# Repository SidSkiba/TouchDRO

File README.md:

# TouchDRO
TocuhDRO PCB Kicad Design

PCB Design Files for a DIY TouchDRO PCB. This is based on information provided by https://www.touchdro.com/

All design done in Kicad 8.

Firmware files provided by https://www.touchdro.com/

All Gerber files included for JLCPCB to manufacture the circuit boards.

Design uses some surface mount components (some 0805 sized resistors and capacitors and sirface mount IC's) so you need to be comfortable with soldering those devices to the board.

Note that ESP32 module needs to be spaced 5mm above the circuit board.

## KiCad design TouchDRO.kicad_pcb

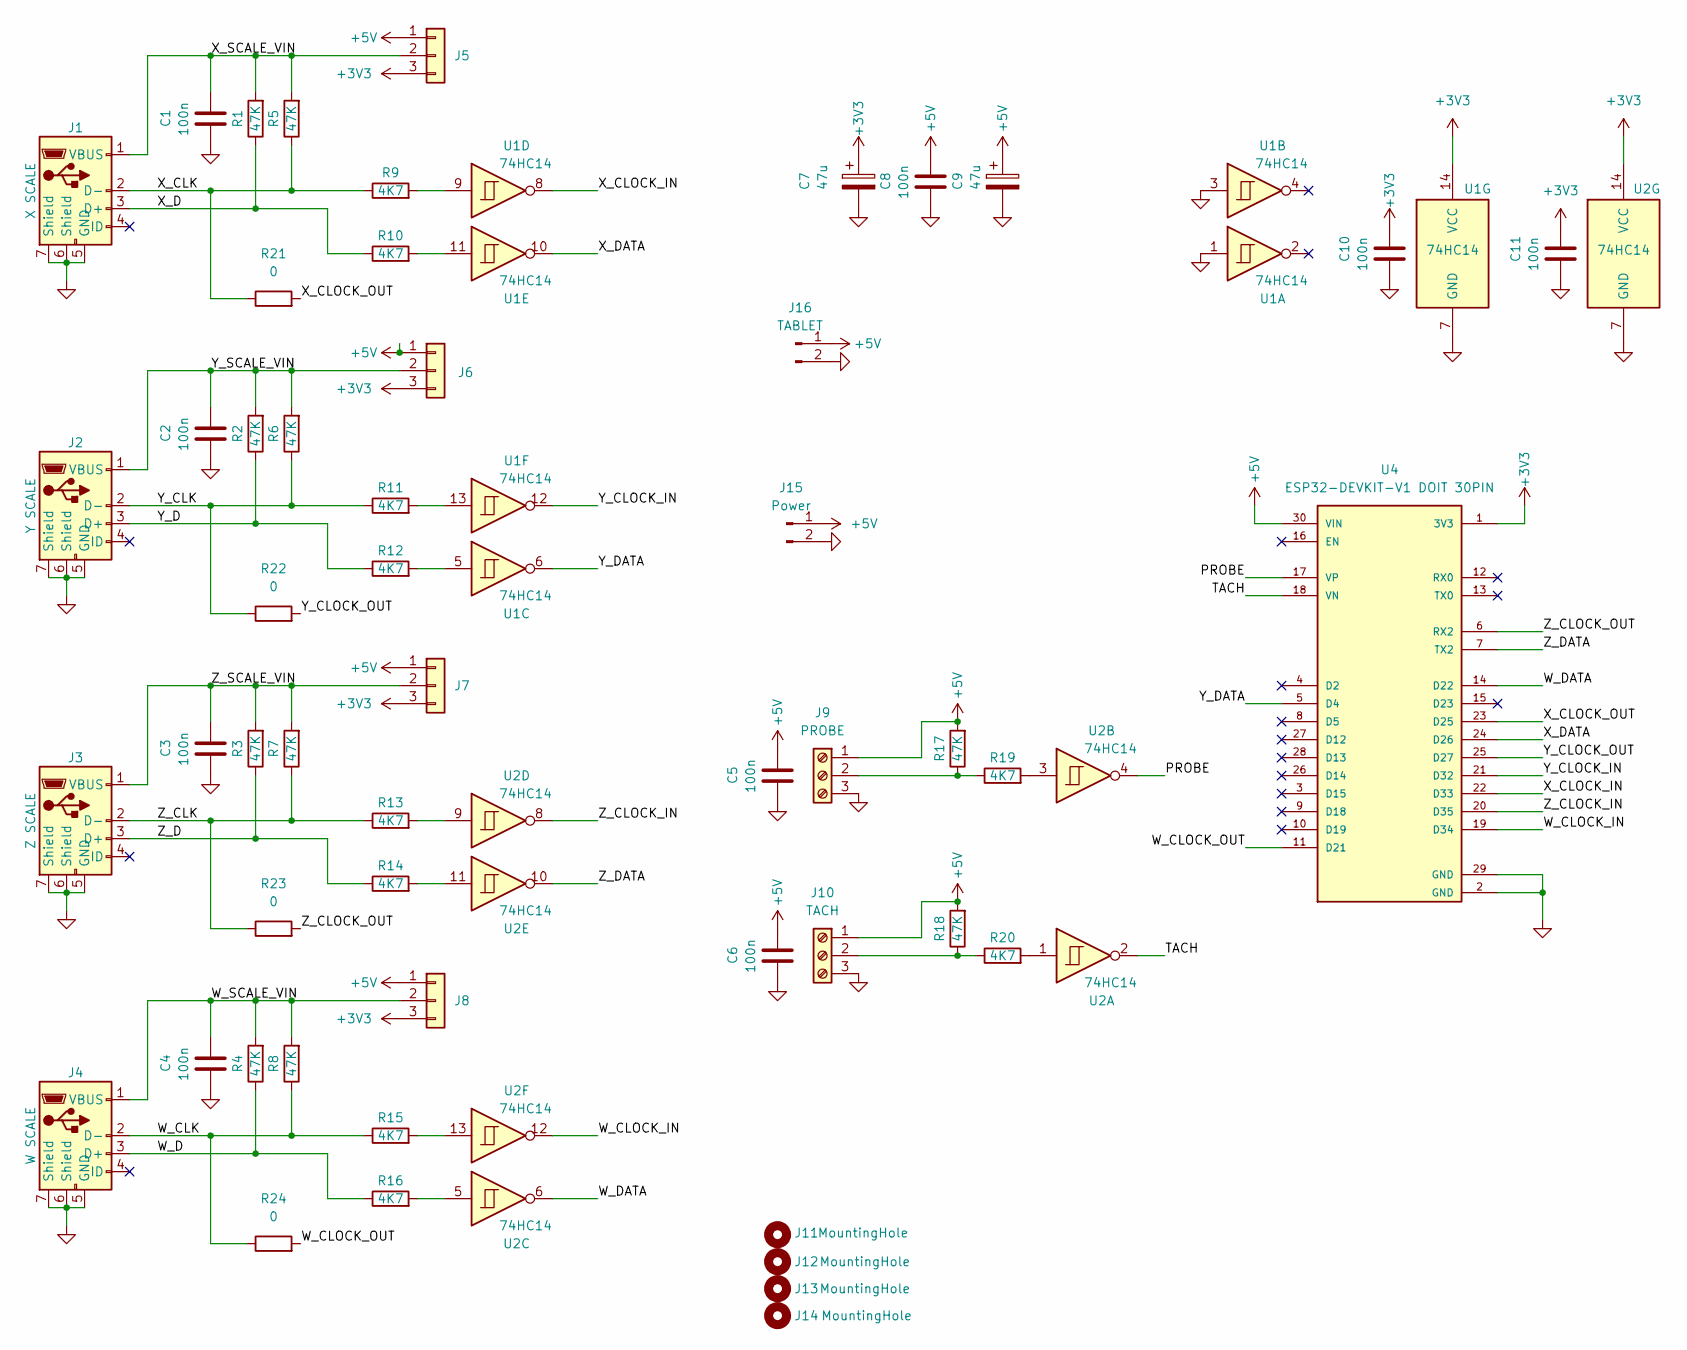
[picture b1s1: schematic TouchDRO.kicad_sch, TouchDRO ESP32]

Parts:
C1, C2, C3, C4, C5, C6, C8, C10, C11: 100n; C_0805_2012Metric_Pad1.18x1.45mm_HandSolder; LCSC C3034534
C7, C9: 47u; CP_Radial_D8.0mm_P3.50mm; LCSC 03EC0571
J1: X SCALE; USB Breakout Board
J2: Y SCALE; USB Breakout Board
J3: Z SCALE; USB Breakout Board
J4: W SCALE; USB Breakout Board
J5: X SCALE; PinHeader_1x03_P2.54mm_Vertical
J6: Y SCALE; PinHeader_1x03_P2.54mm_Vertical
J7: Z SCALE; PinHeader_1x03_P2.54mm_Vertical
J8: W SCALE; PinHeader_1x03_P2.54mm_Vertical
J9: PROBE; TerminalBlock_Phoenix_MPT-0,5-3-2.54_1x03_P2.54mm_Horizontal
J10: TACH; TerminalBlock_Phoenix_MPT-0,5-3-2.54_1x03_P2.54mm_Horizontal
J11, J12, J13, J14: MountingHole; MountingHole_3.5mm
J15: Power; PinHeader_1x02_P2.54mm_Vertical
J16: TABLET; PinHeader_1x02_P2.54mm_Vertical
R1, R2, R3, R4, R5, R6, R7, R8, R17, R18: 47K; R_0805_2012Metric_Pad1.20x1.40mm_HandSolder; LCSC C410613
R9, R10, R11, R12, R13, R14, R15, R16, R19, R20: 4K7; R_Axial_DIN0204_L3.6mm_D1.6mm_P7.62mm_Horizontal; LCSC C119339
R21, R22, R23, R24: 0; R_Axial_DIN0204_L3.6mm_D1.6mm_P7.62mm_Horizontal
U1, U2: 74HC14; 14PIN_SOIC; LCSC C2907
U4: ESP32-DEVKIT-V1 DOIT 30PIN; MODULE_ESP32_DEVKIT_V1 DOIT 30PIN; PARTREV N/A

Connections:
+3V3: C7.1, C10.1, C11.1, J5.3, J6.3, J7.3, J8.3, U1.14 (VCC), U2.14 (VCC), U4.1 (3V3)
+5V: C5.1, C6.1, C8.1, C9.1, J5.1, J6.1, J7.1, J8.1, J9.1, J10.1, J15.1, J16.1, R17.2, R18.2, U4.30 (VIN)
/PROBE: U2.4, U4.17 (VP)
/TACH: U2.2, U4.18 (VN)
/W_CLK: J4.2 (D-), R8.1, R15.1, R24.1
/W_CLOCK_IN: U2.12, U4.19 (D34)
/W_CLOCK_OUT: R24.2, U4.11 (D21)
/W_D: J4.3 (D+), R4.1, R16.1
/W_DATA: U2.6, U4.14 (D22)
/W_SCALE_VIN: C4.1, J4.1 (VBUS), J8.2, R4.2, R8.2
/X_CLK: J1.2 (D-), R5.1, R9.1, R21.1
/X_CLOCK_IN: U1.8, U4.22 (D33)
/X_CLOCK_OUT: R21.2, U4.23 (D25)
/X_D: J1.3 (D+), R1.1, R10.1
/X_DATA: U1.10, U4.24 (D26)
/X_SCALE_VIN: C1.1, J1.1 (VBUS), J5.2, R1.2, R5.2
/Y_CLK: J2.2 (D-), R6.1, R11.1, R22.1
/Y_CLOCK_IN: U1.12, U4.21 (D32)
/Y_CLOCK_OUT: R22.2, U4.25 (D27)
/Y_D: J2.3 (D+), R2.1, R12.1
/Y_DATA: U1.6, U4.5 (D4)
/Y_SCALE_VIN: C2.1, J2.1 (VBUS), J6.2, R2.2, R6.2
/Z_CLK: J3.2 (D-), R7.1, R13.1, R23.1
/Z_CLOCK_IN: U2.8, U4.20 (D35)
/Z_CLOCK_OUT: R23.2, U4.6 (RX2)
/Z_D: J3.3 (D+), R3.1, R14.1
/Z_DATA: U2.10, U4.7 (TX2)
/Z_SCALE_VIN: C3.1, J3.1 (VBUS), J7.2, R3.2, R7.2
GND: C1.2, C2.2, C3.2, C4.2, C5.2, C6.2, C7.2, C8.2, C9.2, C10.2, C11.2, J1.5 (GND), J1.6 (Shield), J1.7 (Shield), J2.5 (GND), J2.6 (Shield), J2.7 (Shield), J3.5 (GND), J3.6 (Shield), J3.7 (Shield), J4.5 (GND), J4.6 (Shield), J4.7 (Shield), J9.3, J10.3, J15.2, J16.2, U1.1, U1.3, U1.7 (GND), U2.7 (GND), U4.2 (GND), U4.29 (GND)
unnamed: J9.2, R17.1, R19.1
unnamed: J10.2, R18.1, R20.1
unnamed: R9.2, U1.9
unnamed: R10.2, U1.11
unnamed: R11.2, U1.13
unnamed: R12.2, U1.5
unnamed: R13.2, U2.9
unnamed: R14.2, U2.11
unnamed: R15.2, U2.13
unnamed: R16.2, U2.5
unnamed: R19.2, U2.3
unnamed: R20.2, U2.1

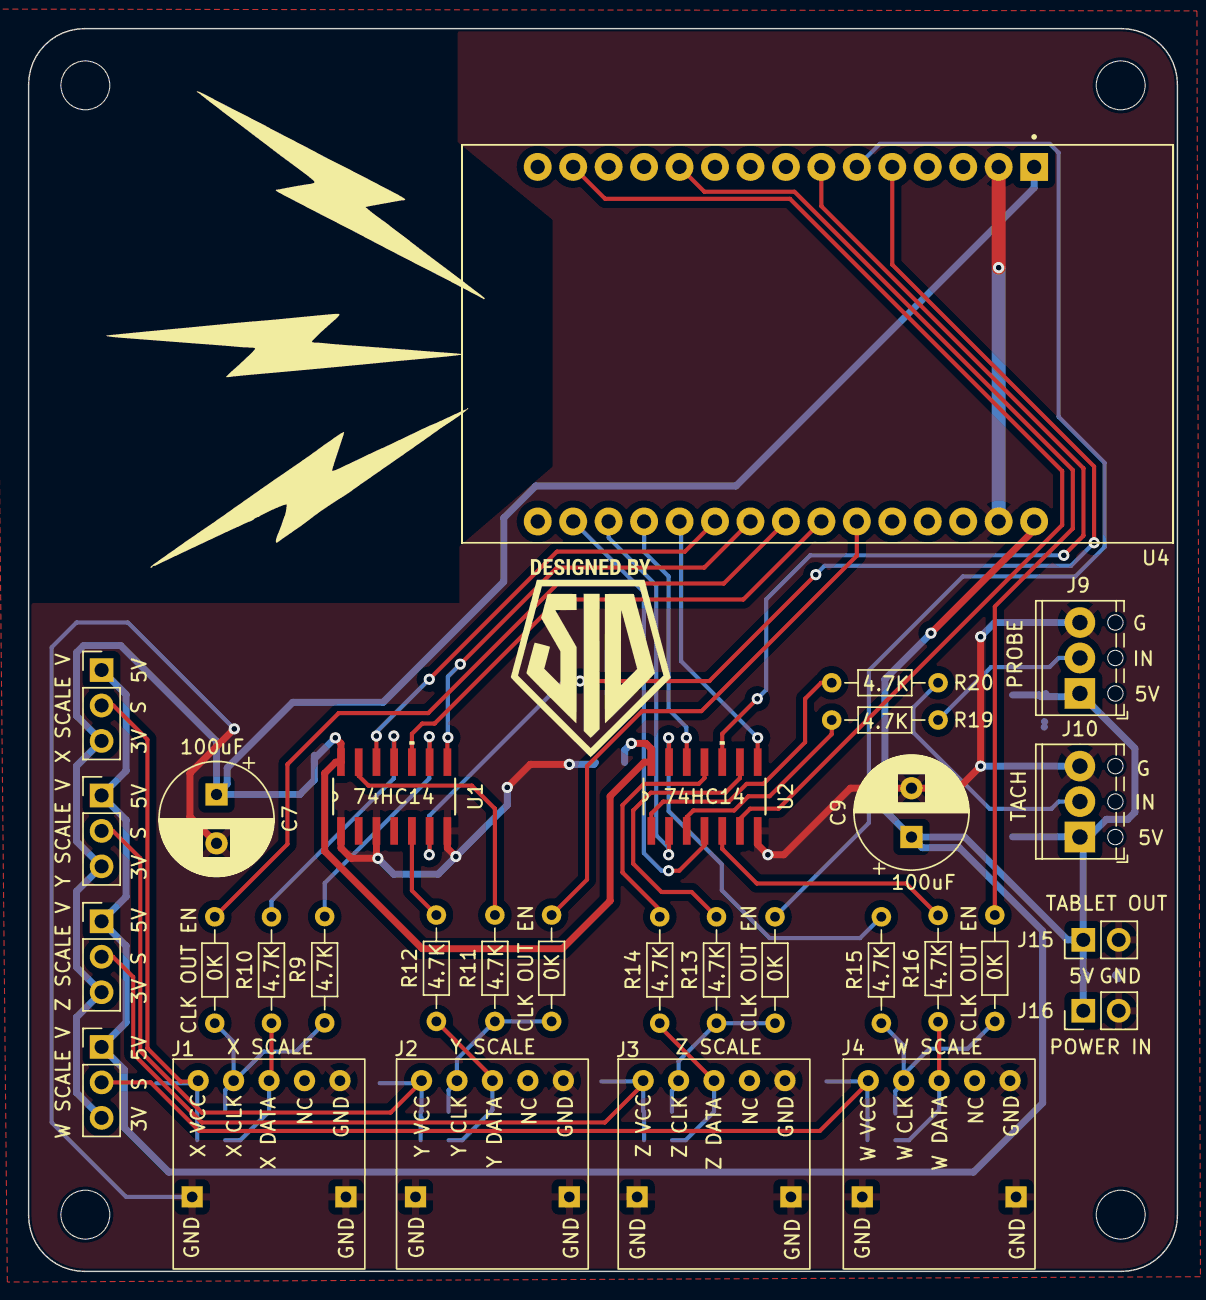
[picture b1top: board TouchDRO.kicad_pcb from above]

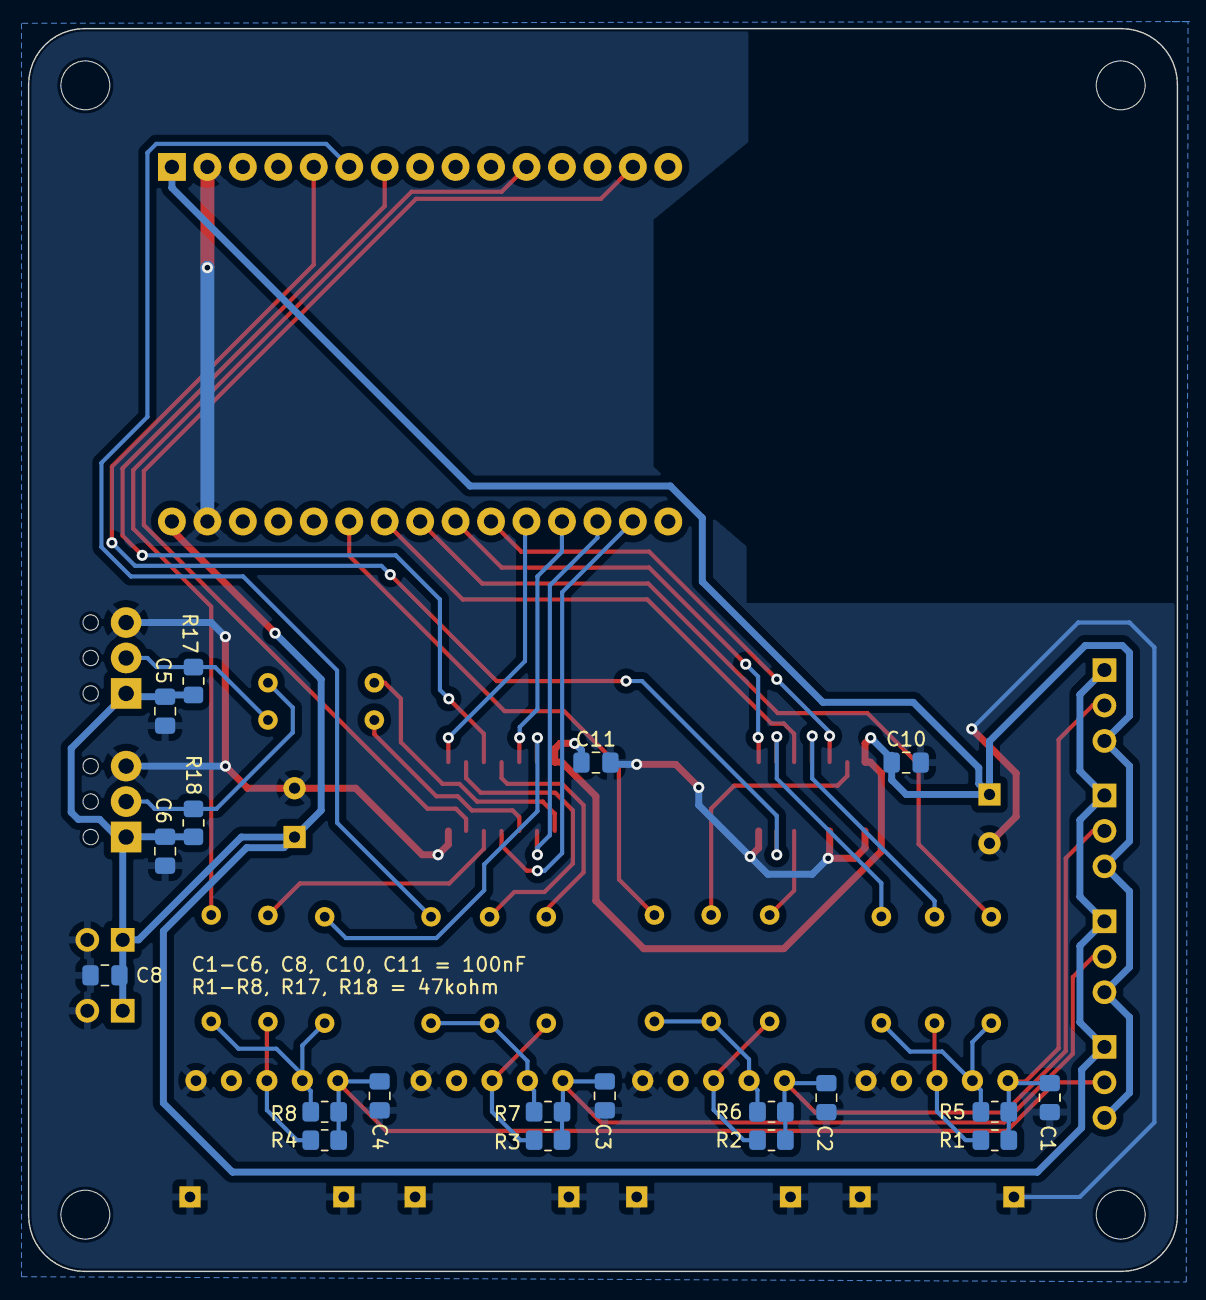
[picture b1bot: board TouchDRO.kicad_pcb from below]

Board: 2 copper layers, 82.3 x 89.0 mm, 54 parts (19 on the bottom side), 41 nets.
